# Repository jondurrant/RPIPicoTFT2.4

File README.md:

# RPIPicoTFT2.4
This is a demonstration of using a MSP2401  2.4 TFT screen driven by ILI9341 from Raspberry PI Pico

The Repo goes along with a video on my [YouTube channel](https://youtu.be/WUGTSiKEeMA)

## Display

The display I used is MSP2401 or a generic version of. Purchased from [Kunkune](https://kunkune.co.uk/shop/kunkune-accessories/lcd-2-4-inch-240x320-spi-tft-lcd-serial-port-module-5v3-3v-pcb-adapter-micro-sd-card/)

## Basic Example
This example demonstrates basic control of the screen to display rectangles.

## Connectivity
		-	12,		//SDO(MISO)
		-	9, 		//CS
		-	10,		//SCK
		-	11,		//SDI(MOSI)
		-	15,  		//RESET
		-	8,			//DC/RS
		-	13, 		//LED

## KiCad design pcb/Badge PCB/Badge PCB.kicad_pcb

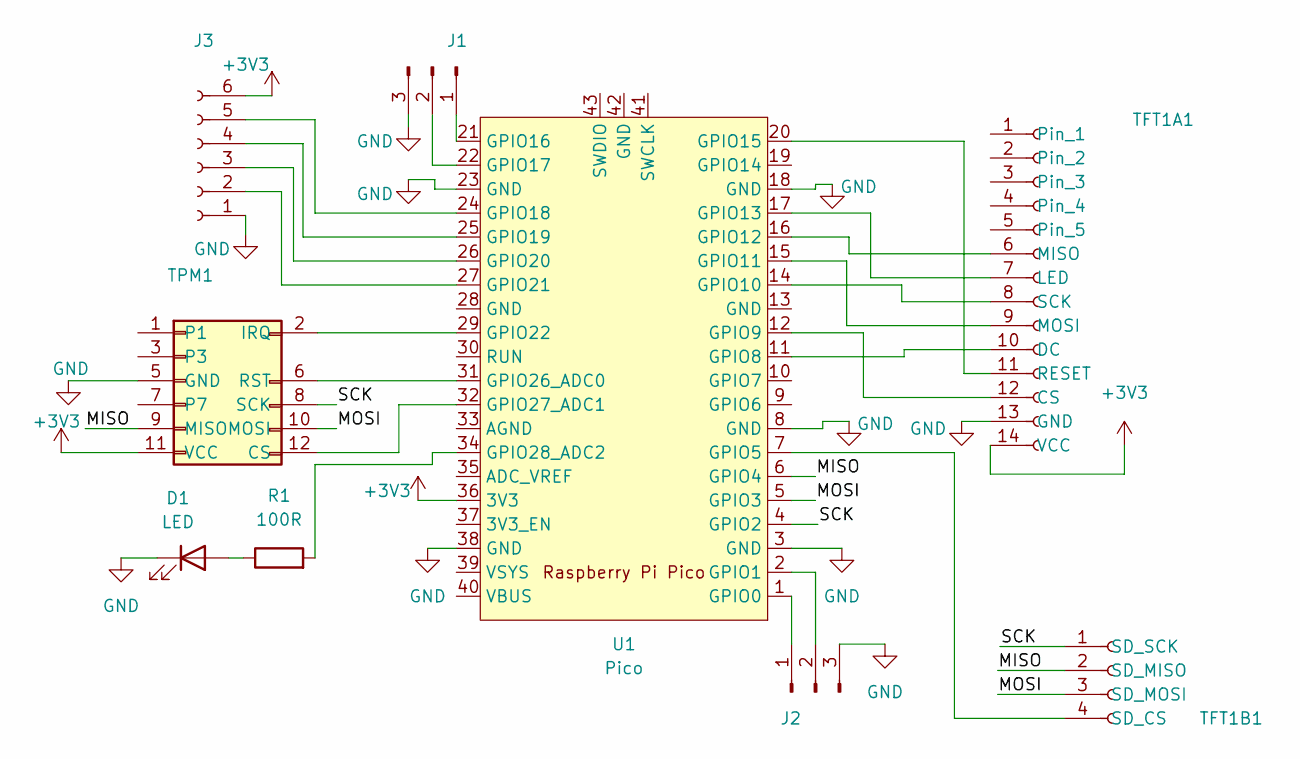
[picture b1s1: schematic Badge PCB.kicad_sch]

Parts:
D1: LED; LED_D1.8mm_W3.3mm_H2.4mm
J1, J2: Conn_01x02_Male; PinSocket_1x03_P2.54mm_Vertical
J3: Conn_01x06_Female; PinSocket_1x06_P2.54mm_Vertical
R1: 100R; R_Axial_DIN0207_L6.3mm_D2.5mm_P10.16mm_Horizontal
TFT1A1: Conn_01x14_Female; PinSocket_1x14_P2.54mm_Vertical
TFT1B1: Conn_01x04_Female; PinSocket_1x04_P2.54mm_Vertical
TPM1: Conn_02x06_Odd_Even; PinHeader_2x06_P2.54mm_Horizontal
U1: Pico; MODULE_SC0918

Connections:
+3V3: J3.6, TFT1A1.14 (VCC), TPM1.11 (VCC), U1.36 (3V3)
/MISO: TFT1B1.2 (SD_MISO), TPM1.9 (MISO), U1.6 (GPIO4)
/MOSI: TFT1B1.3 (SD_MOSI), TPM1.10 (MOSI), U1.5 (GPIO3)
/SCK: TFT1B1.1 (SD_SCK), TPM1.8 (SCK), U1.4 (GPIO2)
GND: D1.1 (K), J1.3, J2.3, J3.1, TFT1A1.13 (GND), TPM1.4, TPM1.5 (GND), U1.3 (GND), U1.8 (GND), U1.18 (GND), U1.23 (GND), U1.38 (GND)
unnamed: J2.1, U1.1 (GPIO0)
unnamed: J3.2, U1.27 (GPIO21)
unnamed: J3.3, U1.26 (GPIO20)
unnamed: J3.4, U1.25 (GPIO19)
unnamed: J3.5, U1.24 (GPIO18)
unnamed: D1.2 (A), R1.1
unnamed: TFT1A1.6 (MISO), U1.16 (GPIO12)
unnamed: TFT1A1.7 (LED), U1.17 (GPIO13)
unnamed: TFT1A1.8 (SCK), U1.14 (GPIO10)
unnamed: TFT1A1.9 (MOSI), U1.15 (GPIO11)
unnamed: TFT1A1.10 (DC), U1.11 (GPIO8)
unnamed: TFT1A1.11 (RESET), U1.20 (GPIO15)
unnamed: TFT1A1.12 (CS), U1.12 (GPIO9)
unnamed: J2.2, U1.2 (GPIO1)
unnamed: TFT1B1.4 (SD_CS), U1.7 (GPIO5)
unnamed: J1.1, U1.21 (GPIO16)
unnamed: J1.2, U1.22 (GPIO17)
unnamed: TPM1.2 (IRQ), U1.29 (GPIO22)
unnamed: TPM1.6 (RST), U1.31 (GPIO26_ADC0)
unnamed: TPM1.12 (CS), U1.32 (GPIO27_ADC1)
unnamed: R1.2, U1.34 (GPIO28_ADC2)

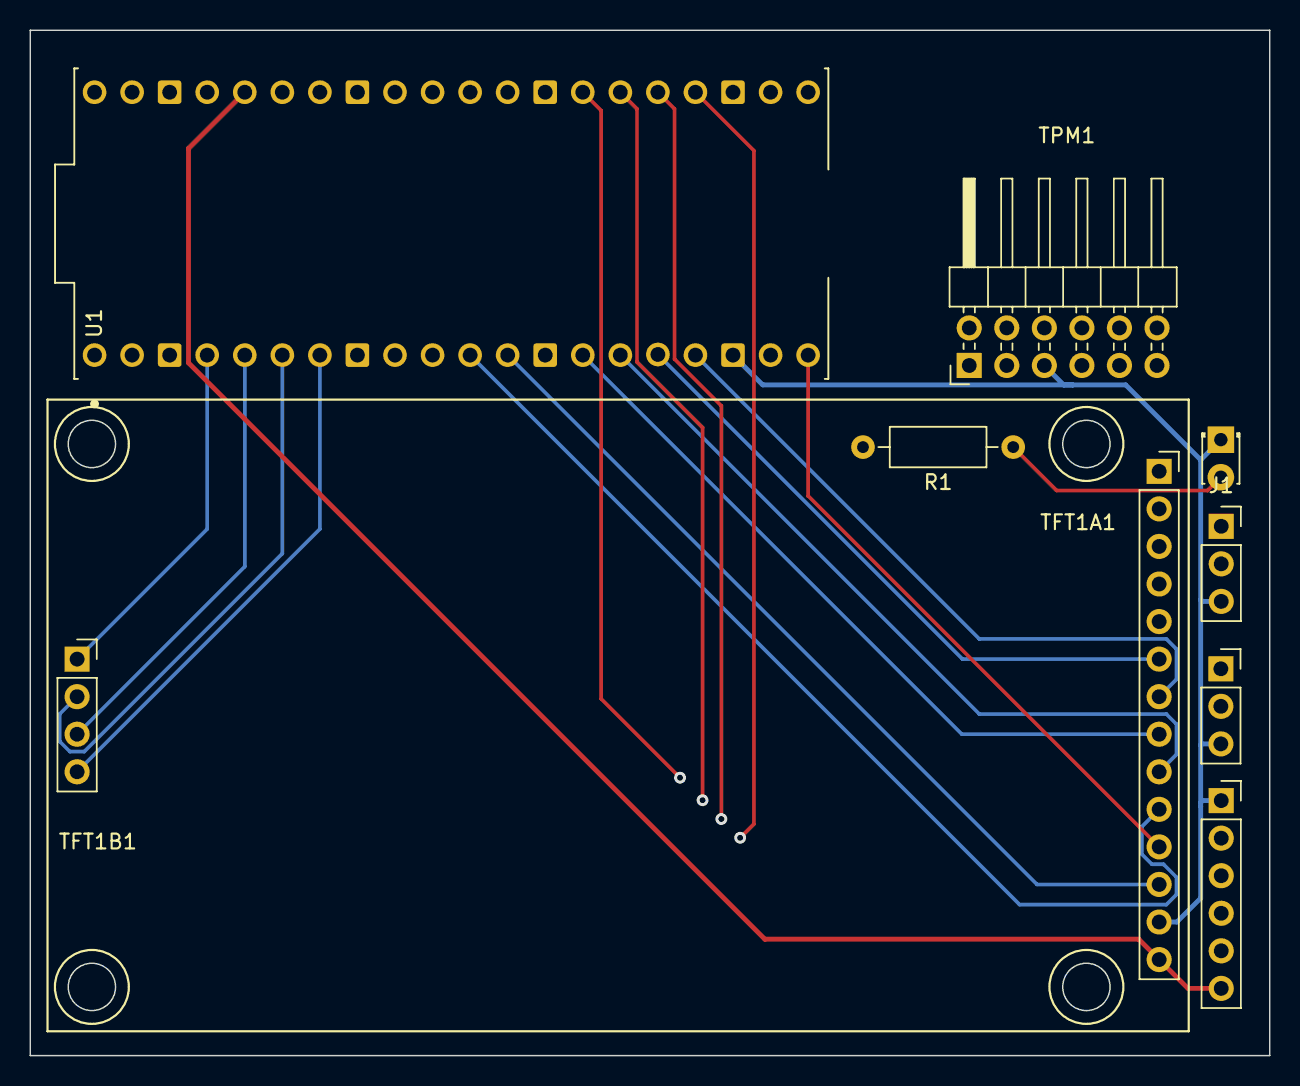
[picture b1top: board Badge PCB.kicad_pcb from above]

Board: 4 copper layers, 83.8 x 69.3 mm, 9 parts (0 on the bottom side), 26 nets.

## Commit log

2024-05-13 initial version
2024-05-21 Adding PCB Design
2024-05-23 SD Card Example
